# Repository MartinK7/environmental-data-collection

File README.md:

# Environmental-data-collection

##  TASK
Cílem projektu je sestavit systém, který bude schopen monitorovat vybrané meteorologická, případně hydropedologická data a odesílat je na servery pro IoT jako např. Thing Network, ThingSpeak, ubidots, aj. Snahou bude získaná data nejen archivovat, ale poskytnout je některé z předpovědních sítí jako OpenWeather, Weather Underground apod. MP(K)C-M2E: Prostudujte dostupné koncepce pro měření vybraných meteorologických veličin. Prostudujte možnosti řídícího prvku měřícího systému např. AVR, Raspberry Pi, STM32, ESP, aj. a zvolte ideální variantu. Prostudujte vhodné komunikační rozhraní pro přenos dat. Vyberte veškeré komponenty, navrhněte blokové schéma zařízení, sestavte obvodové zapojení, DPS a realizujte je. Při návrhu dbejte na nízkou spotřebu finálního zařízení a odolnost ve venkovním prostředí. MP(K)C-MSE: Zařízení zkompletujte, oživte, naprogramujte obslužné firmwary a zprovozněte sběr dat. Proveďte detailní testování celého systému a porovnejte jej s jinými řešeními. Měřená data poskytněte některé ze sítě pro sběr a předpověď počasí. Pozn.: Systém bude v budoucnu nasazen pro měřící stanici na střeše URELu. Výhodou je zkušenost s vývojem elektroniky a s programováním v jazyce C/C++ nebo Python.

## Basic literary sources
[1] KOUSAL, Martin. IoT monitoring ovzduší. Brno: Vysoké učení technické v Brně, Fakulta elektrotechniky a komunikačních technologií, Ústav radioelektroniky, 2022, 68 s. Bakalářská práce. Vedoucí práce: doc. Ing. Tomáš Frýza, Ph.D.

[2] Weather stations. OpenWeather [online]. 2022 [cit. 2022-05-24]. Dostupné z: https://openweathermap.org/stations

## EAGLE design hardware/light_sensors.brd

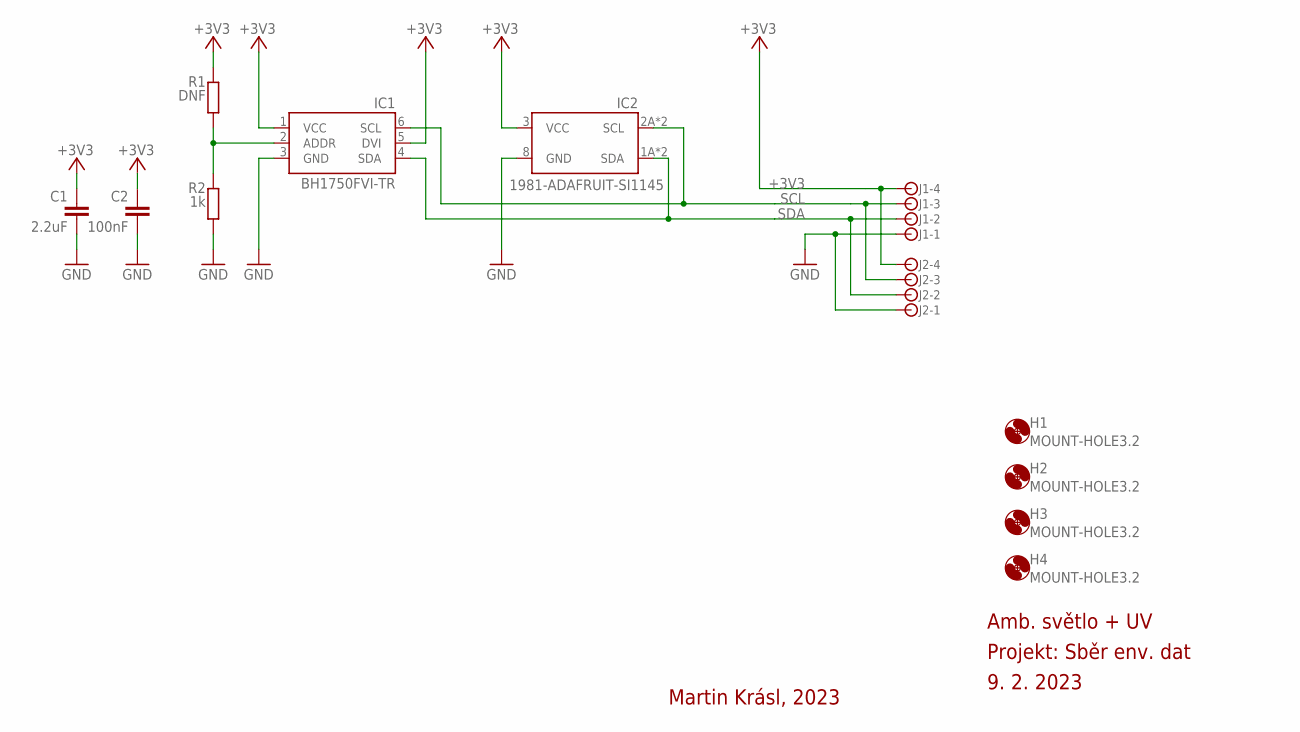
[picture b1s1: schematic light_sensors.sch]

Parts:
C1: 2.2uF; C0805
C2: 100nF; C0402
H1, H2, H3, H4: MOUNT-HOLE3.2; 3,2
IC1: BH1750FVI-TR; WSOF6
IC2: 1981-ADAFRUIT-SI1145
J1, J2: JST-XH-4; B4B-XH-A
R1: DNF; R0402
R2: 1k; R0402

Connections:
+3V3: C1.1, C2.1, IC1.1 (VCC), IC1.5 (DVI), IC2.3 (VCC), J1.4, J2.4, R1.2
GND: C1.2, C2.2, IC1.3 (GND), IC2.8 (GND), J1.1, J2.1, R2.1
unnamed: IC1.2 (ADDR), R1.1, R2.2
SCL: IC1.6 (SCL), IC2.2A (SCL), IC2.2B (SCL), J1.3, J2.3
SDA: IC1.4 (SDA), IC2.1A (SDA), IC2.1B (SDA), J1.2, J2.2

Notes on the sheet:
Amb. světlo + UV
Projekt: Sběr env. dat
9. 2. 2023
Martin Krásl, 2023

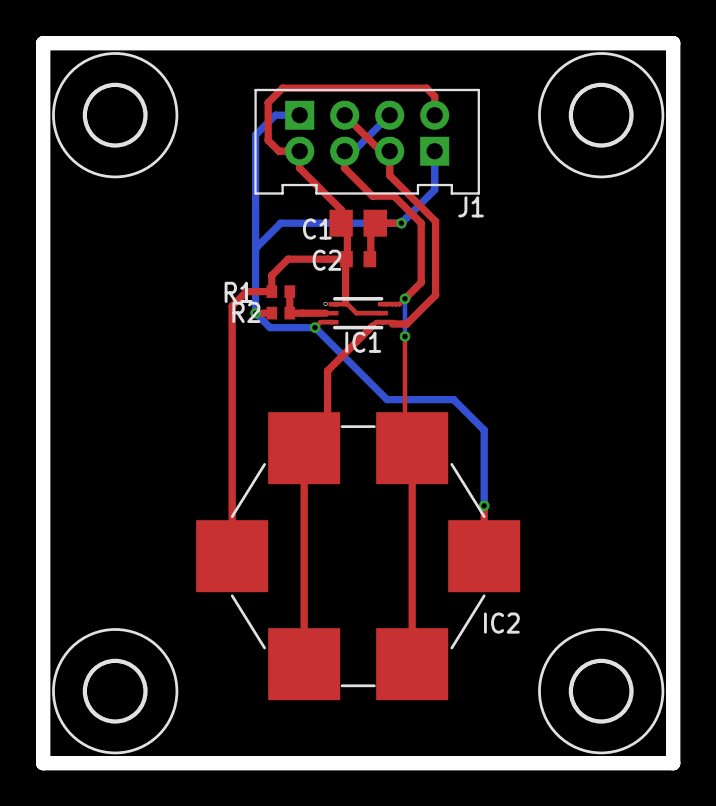
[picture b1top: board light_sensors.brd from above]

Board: 2 copper layers, 35.0 x 40.0 mm, 12 parts (1 on the bottom side), 5 nets.

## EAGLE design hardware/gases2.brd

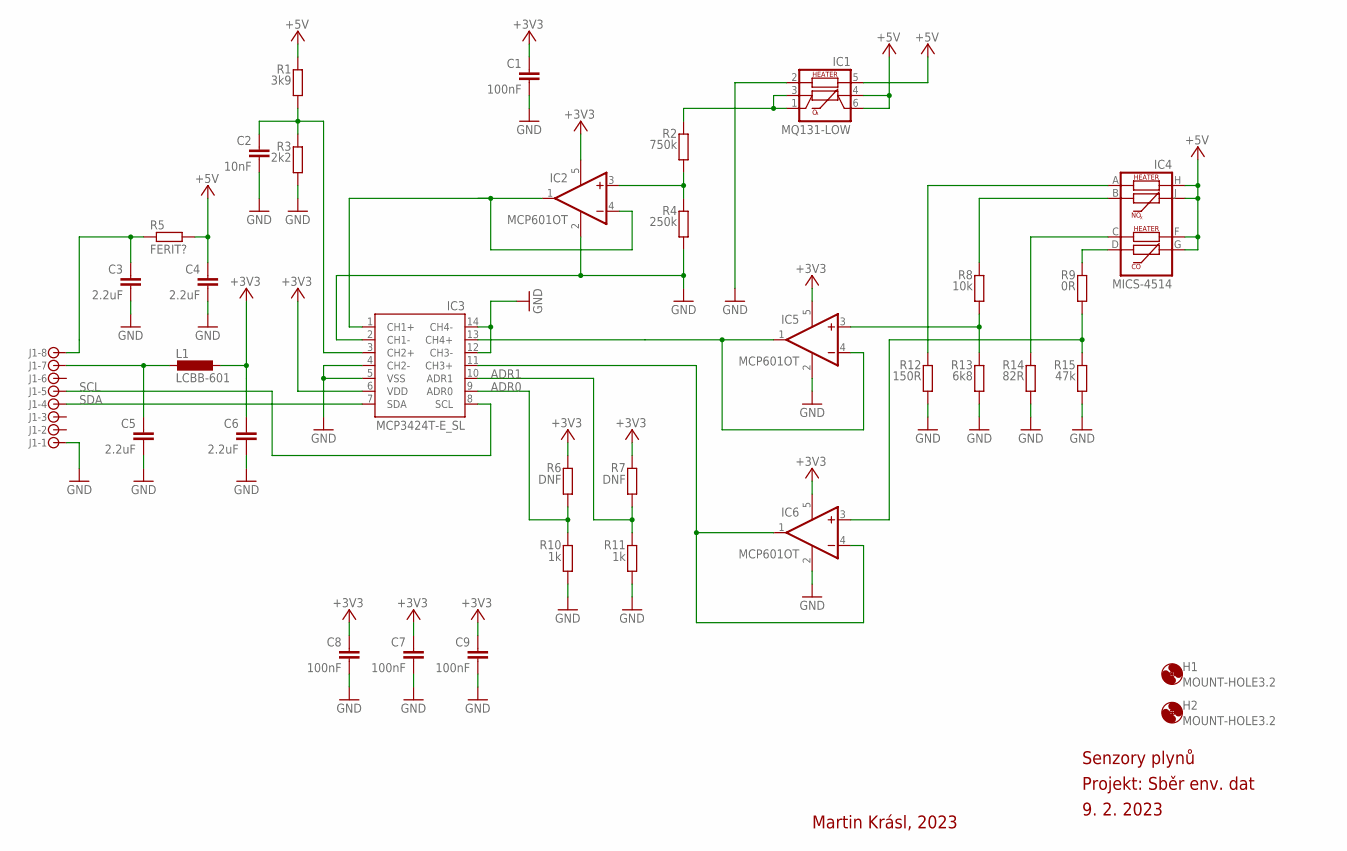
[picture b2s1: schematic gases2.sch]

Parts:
C1, C7, C8, C9: 100nF; C0402
C2: 10nF; C0402
C3, C4, C5, C6: 2.2uF; C0402
H1, H2: MOUNT-HOLE3.2; 3,2
IC1: MQ131-LOW
IC2, IC5, IC6: MCP601OT; SOT23-5
IC3: MCP3424T-E_SL; SOIC127P600X175-14N
IC4: MICS-4514
J1: JST-XH-8; B8B-XH-A
L1: LCBB-601; L2012C
R1: 3k9; R0402
R2: 750k; R0402
R3: 2k2; R0402
R4: 250k; R0402
R5: FERIT?; R0805
R6, R7: DNF; R0402
R8: 10k; R0402
R9: 0R; R0402
R10, R11: 1k; R0402
R12: 150R; R1206
R13: 6k8; R0402
R14: 82R; R1206
R15: 47k; R0402

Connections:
+3V3: C1.1, C6.1, C7.1, C8.1, C9.1, IC2.5 (V+), IC3.6 (VDD), IC5.5 (V+), IC6.5 (V+), L1.1, R6.2, R7.2
+5V: C4.1, IC1.4, IC1.5, IC1.6, IC4.F, IC4.G, IC4.H, IC4.J, R1.2, R5.2
ADR0: IC3.9 (ADR0), R6.1, R10.2
ADR1: IC3.10 (ADR1), R7.1, R11.2
GND: C1.2, C2.2, C3.2, C4.2, C5.2, C6.2, C7.2, C8.2, C9.2, IC1.2, IC2.2 (V-), IC3.2 (CH1-), IC3.4 (CH2-), IC3.5 (VSS), IC3.12 (CH3-), IC3.14 (CH4-), IC5.2 (V-), IC6.2 (V-), J1.1, R3.1, R4.1, R10.1, R11.1, R12.1, R13.1, R14.1, R15.1
unnamed: IC2.1 (OUT), IC2.4 (-IN), IC3.1 (CH1+)
unnamed: C2.1, IC3.3 (CH2+), R1.1, R3.2
unnamed: C3.1, J1.8, R5.1
unnamed: IC2.3 (+IN), R2.1, R4.2
unnamed: IC1.1, IC1.3, R2.2
unnamed: IC4.B, R8.2
unnamed: IC4.D, R9.2
unnamed: IC5.3 (+IN), R8.1, R13.2
unnamed: IC4.A, R12.2
unnamed: IC4.C, R14.2
unnamed: C5.1, J1.7, L1.2
unnamed: IC6.3 (+IN), R9.1, R15.2
unnamed: IC3.13 (CH4+), IC5.1 (OUT), IC5.4 (-IN)
unnamed: IC3.11 (CH3+), IC6.1 (OUT), IC6.4 (-IN)
SCL: IC3.8 (SCL), J1.5
SDA: IC3.7 (SDA), J1.4

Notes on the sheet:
Senzory plynů
Projekt: Sběr env. dat
9. 2. 2023
Martin Krásl, 2023

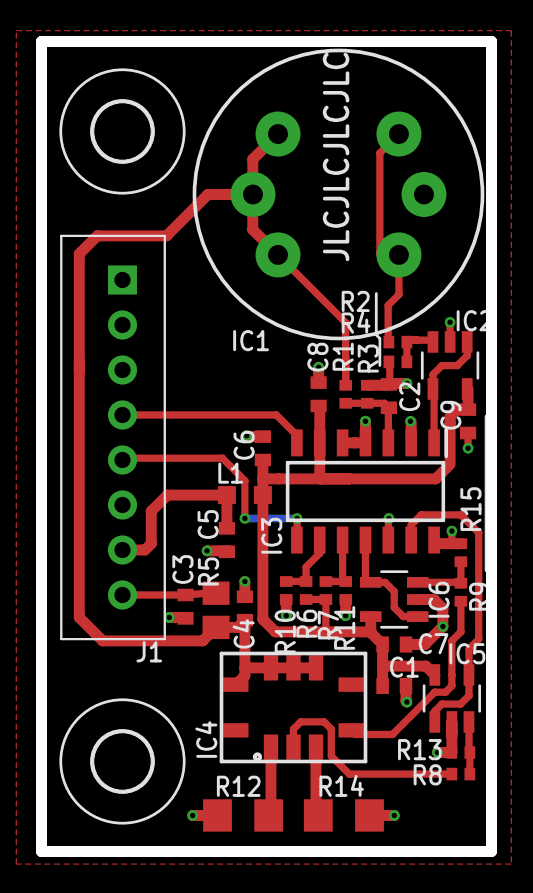
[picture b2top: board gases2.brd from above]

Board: 2 copper layers, 25.0 x 45.0 mm, 34 parts (0 on the bottom side), 21 nets.

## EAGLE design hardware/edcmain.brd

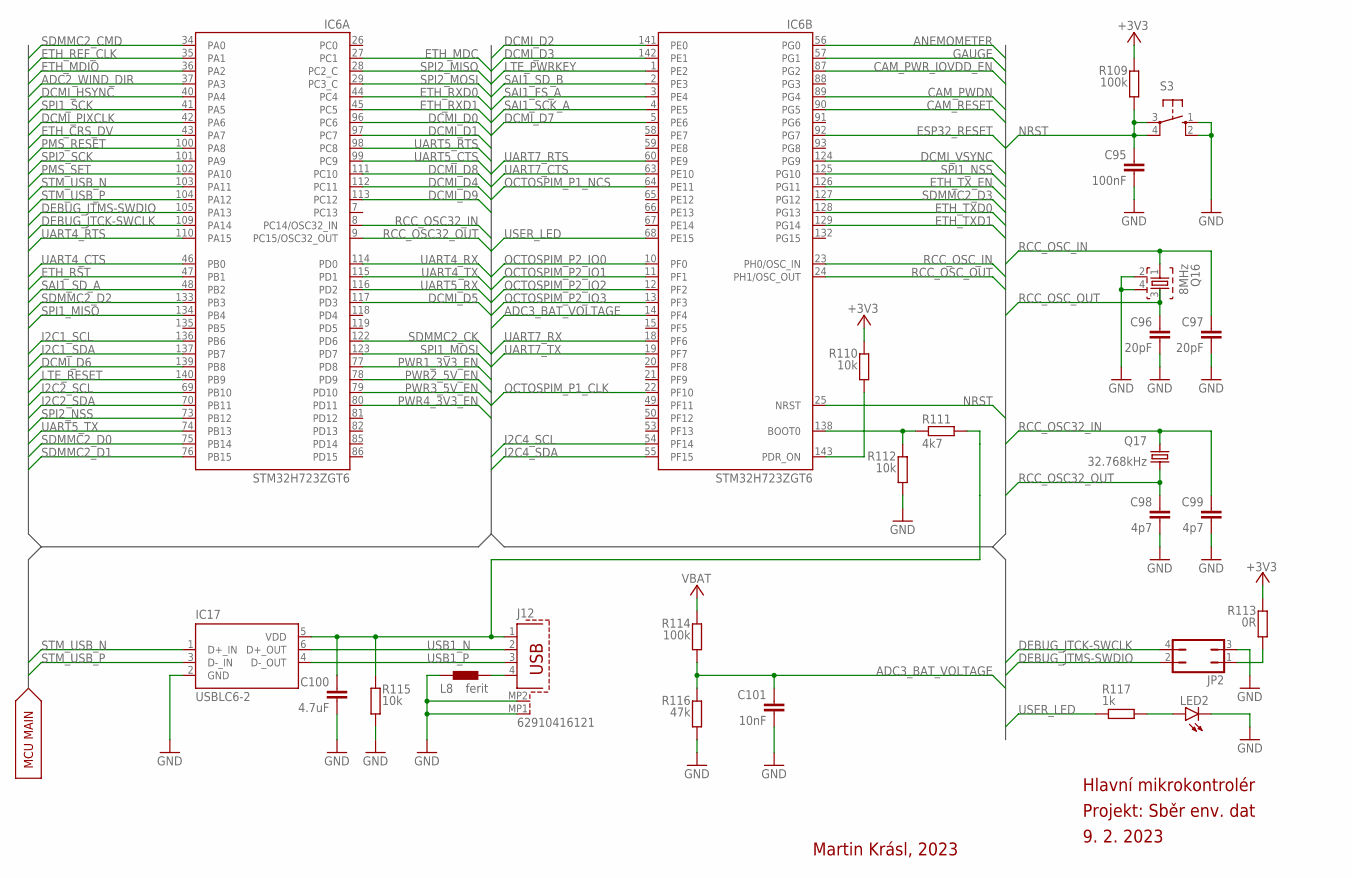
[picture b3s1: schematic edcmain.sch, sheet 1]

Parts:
C95: 100nF; C0402
C96, C97: 20pF; C0402
C98, C99: 4p7; C0402
C100: 4.7uF; C0402
C101: 10nF; C0402
IC6: STM32H723ZGT6; QFP50P2200X2200X160-144N
IC17: USBLC6-2; SOT23-6
J12: 62910416121
JP2: JP2Q
L8: ferit; 0402
LED2: LEDCHIP-LED0805; CHIP-LED0805
Q16: 8MHz; CRYSTAL3.2X2.5
Q17: 32.768kHz; NX3215SA32768KEXS00AMU00003
R109, R114: 100k; R0402
R110, R112, R115: 10k; R0402
R111: 4k7; R0402
R113: 0R; R0402
R116: 47k; R0402
R117: 1k; R0402
S3: 10-XX; B3F-10XX

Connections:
+3V3: R109.2, R110.2, R113.2; also elsewhere on the board
ADC2_WIND_DIR: IC6.37 (PA3); also elsewhere on the board
ADC3_BAT_VOLTAGE: C101.1, IC6.14 (PF4), R114.1, R116.2
ANEMOMETER: IC6.56 (PG0); also elsewhere on the board
CAM_PWDN: IC6.89 (PG4); also elsewhere on the board
CAM_PWR_IOVDD_EN: IC6.87 (PG2); also elsewhere on the board
CAM_RESET: IC6.90 (PG5); also elsewhere on the board
DCMI_D0: IC6.96 (PC6); also elsewhere on the board
DCMI_D1: IC6.97 (PC7); also elsewhere on the board
DCMI_D2: IC6.141 (PE0); also elsewhere on the board
DCMI_D3: IC6.142 (PE1); also elsewhere on the board
DCMI_D4: IC6.112 (PC11); also elsewhere on the board
DCMI_D5: IC6.117 (PD3); also elsewhere on the board
DCMI_D6: IC6.139 (PB8); also elsewhere on the board
DCMI_D7: IC6.5 (PE6); also elsewhere on the board
DCMI_D8: IC6.111 (PC10); also elsewhere on the board
DCMI_D9: IC6.113 (PC12); also elsewhere on the board
DCMI_HSYNC: IC6.40 (PA4); also elsewhere on the board
DCMI_PIXCLK: IC6.42 (PA6); also elsewhere on the board
DCMI_VSYNC: IC6.124 (PG9); also elsewhere on the board
DEBUG_JTCK-SWCLK: IC6.109 (PA14), JP2.4
DEBUG_JTMS-SWDIO: IC6.105 (PA13), JP2.2
ESP32_RESET: IC6.92 (PG7); also elsewhere on the board
ETH_CRS_DV: IC6.43 (PA7); also elsewhere on the board
ETH_MDC: IC6.27 (PC1); also elsewhere on the board
ETH_MDIO: IC6.36 (PA2); also elsewhere on the board
ETH_REF_CLK: IC6.35 (PA1); also elsewhere on the board
ETH_RST: IC6.47 (PB1); also elsewhere on the board
ETH_RXD0: IC6.44 (PC4); also elsewhere on the board
ETH_RXD1: IC6.45 (PC5); also elsewhere on the board
ETH_TXD0: IC6.128 (PG13); also elsewhere on the board
ETH_TXD1: IC6.129 (PG14); also elsewhere on the board
ETH_TX_EN: IC6.126 (PG11); also elsewhere on the board
GAUGE: IC6.57 (PG1); also elsewhere on the board
GND: C95.2, C96.2, C97.2, C98.2, C99.2, C100.2, C101.2, IC17.2 (GND), J12.MP1, J12.MP2, JP2.3, L8.1, LED2.C, Q16.2, Q16.4, R112.1, R115.1, R116.1, S3.1 (S), S3.2 (S1); also elsewhere on the board
I2C1_SCL: IC6.136 (PB6); also elsewhere on the board
I2C1_SDA: IC6.137 (PB7); also elsewhere on the board
I2C2_SCL: IC6.69 (PB10); also elsewhere on the board
I2C2_SDA: IC6.70 (PB11); also elsewhere on the board
I2C4_SCL: IC6.54 (PF14); also elsewhere on the board
I2C4_SDA: IC6.55 (PF15); also elsewhere on the board
LTE_PWRKEY: IC6.1 (PE2); also elsewhere on the board
LTE_RESET: IC6.140 (PB9); also elsewhere on the board
unnamed: C100.1, IC17.5 (VDD), J12.1, R111.2, R115.2
unnamed: LED2.A, R117.2
unnamed: IC6.143 (PDR_ON), R110.1
unnamed: IC6.138 (BOOT0), R111.1, R112.2
unnamed: J12.4, L8.2
unnamed: JP2.1, R113.1
NRST: C95.1, IC6.25 (NRST), R109.1, S3.3, S3.4 (P1)
OCTOSPIM_P1_CLK: IC6.22 (PF10); also elsewhere on the board
OCTOSPIM_P1_NCS: IC6.64 (PE11); also elsewhere on the board
OCTOSPIM_P2_IO0: IC6.10 (PF0); also elsewhere on the board
OCTOSPIM_P2_IO1: IC6.11 (PF1); also elsewhere on the board
OCTOSPIM_P2_IO2: IC6.12 (PF2); also elsewhere on the board
OCTOSPIM_P2_IO3: IC6.13 (PF3); also elsewhere on the board
PMS_RESET: IC6.100 (PA8); also elsewhere on the board
PMS_SET: IC6.102 (PA10); also elsewhere on the board
PWR1_3V3_EN: IC6.77 (PD8); also elsewhere on the board
PWR2_5V_EN: IC6.78 (PD9); also elsewhere on the board
PWR3_5V_EN: IC6.79 (PD10); also elsewhere on the board
PWR4_3V3_EN: IC6.80 (PD11); also elsewhere on the board
RCC_OSC32_IN: C99.1, IC6.8 (PC14/OSC32_IN), Q17.2
RCC_OSC32_OUT: C98.1, IC6.9 (PC15/OSC32_OUT), Q17.1
RCC_OSC_IN: C97.1, IC6.23 (PH0/OSC_IN), Q16.1
RCC_OSC_OUT: C96.1, IC6.24 (PH1/OSC_OUT), Q16.3
SAI1_FS_A: IC6.3 (PE4); also elsewhere on the board
SAI1_SCK_A: IC6.4 (PE5); also elsewhere on the board
SAI1_SD_A: IC6.48 (PB2); also elsewhere on the board
SAI1_SD_B: IC6.2 (PE3); also elsewhere on the board
SDMMC2_CK: IC6.122 (PD6); also elsewhere on the board
SDMMC2_CMD: IC6.34 (PA0); also elsewhere on the board
SDMMC2_D0: IC6.75 (PB14); also elsewhere on the board
SDMMC2_D1: IC6.76 (PB15); also elsewhere on the board
SDMMC2_D2: IC6.133 (PB3); also elsewhere on the board
SDMMC2_D3: IC6.127 (PG12); also elsewhere on the board
SPI1_MISO: IC6.134 (PB4); also elsewhere on the board
SPI1_MOSI: IC6.123 (PD7); also elsewhere on the board
SPI1_NSS: IC6.125 (PG10); also elsewhere on the board
SPI1_SCK: IC6.41 (PA5); also elsewhere on the board
SPI2_MISO: IC6.28 (PC2_C); also elsewhere on the board
SPI2_MOSI: IC6.29 (PC3_C); also elsewhere on the board
SPI2_NSS: IC6.73 (PB12); also elsewhere on the board
SPI2_SCK: IC6.101 (PA9); also elsewhere on the board
STM_USB_N: IC6.103 (PA11), IC17.1 (D+_IN)
STM_USB_P: IC6.104 (PA12), IC17.3 (D-_IN)
UART4_CTS: IC6.46 (PB0); also elsewhere on the board
UART4_RTS: IC6.110 (PA15); also elsewhere on the board
UART4_RX: IC6.114 (PD0); also elsewhere on the board
UART4_TX: IC6.115 (PD1); also elsewhere on the board
UART5_CTS: IC6.99 (PC9); also elsewhere on the board
UART5_RTS: IC6.98 (PC8); also elsewhere on the board
UART5_RX: IC6.116 (PD2); also elsewhere on the board
UART5_TX: IC6.74 (PB13); also elsewhere on the board
UART7_CTS: IC6.63 (PE10); also elsewhere on the board
UART7_RTS: IC6.60 (PE9); also elsewhere on the board
UART7_RX: IC6.18 (PF6); also elsewhere on the board
UART7_TX: IC6.19 (PF7); also elsewhere on the board
USB1_N: IC17.6 (D+_OUT), J12.2
USB1_P: IC17.4 (D-_OUT), J12.3
USER_LED: IC6.68 (PE15), R117.1
VBAT: R114.2; also elsewhere on the board

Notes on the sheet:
MCU MAIN
Hlavní mikrokontrolér
Projekt: Sběr env. dat
9. 2. 2023
Martin Krásl, 2023

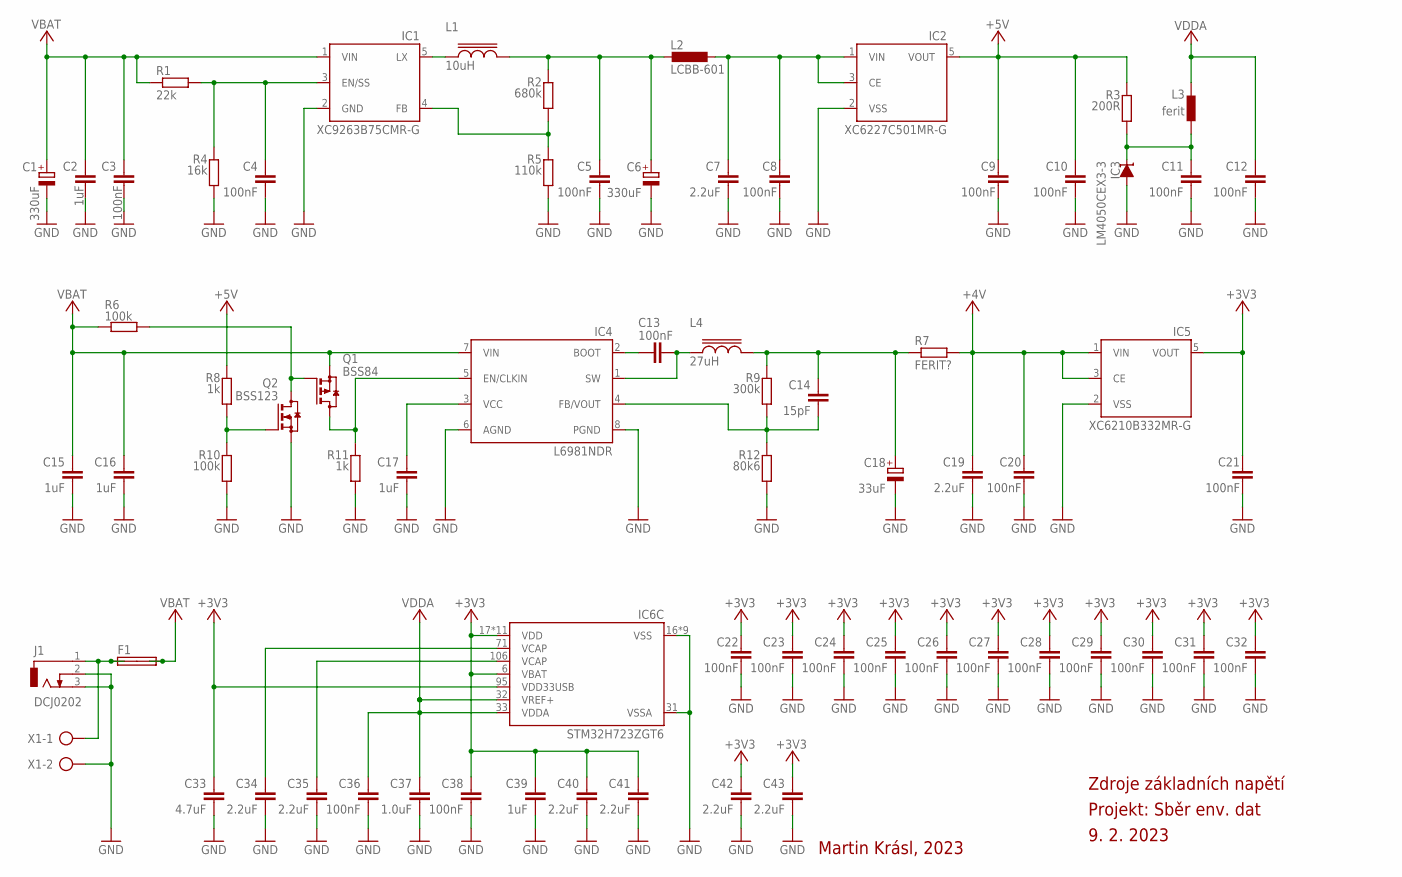
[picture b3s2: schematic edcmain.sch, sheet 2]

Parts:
C1, C6: 330uF; PANASONIC_G
C2, C15, C16: 1uF; C0805
C3, C4, C5, C8, C9, C10, C11, C12, C13, C20, C21, C22, C23, C24, C25, C26, C27, C28, C29, C30, C31, C32, C36, C38: 100nF; C0402
C7, C34, C35, C43: 2.2uF; C0805
C14: 15pF; C0402
C17, C39: 1uF; C0402
C18: 33uF; PANASONIC_G
C19, C40, C41, C42: 2.2uF; C0402
C33: 4.7uF; C0402
C37: 1.0uF; C0402
F1: SHK20L
IC1: XC9263B75CMR-G; SOT95P280X130-5N
IC2: XC6227C501MR-G; SOT95P280X130-5N
IC3: LM4050CEX3-3; SC70-3
IC4: L6981NDR; SOIC127P600X175-8N
IC5: XC6210B332MR-G; SOT95P280X130-5N
IC6: STM32H723ZGT6; QFP50P2200X2200X160-144N
IMG1: IMAGEPRINT; RD_14_24_PRINT
J1: DCJ0202
L1: 10uH; L6
L2: LCBB-601; L2012C
L3: ferit; 0402
L4: 27uH; L6
Q1: BSS84; SOT23
Q2: BSS123; SOT23
R1: 22k; R0402
R2: 680k; R0402
R3: 200R; R0402
R4: 16k; R0402
R5: 110k; R0402
R6, R10: 100k; R0402
R7: FERIT?; R2010
R8, R11: 1k; R0402
R9: 300k; R0402
R12: 80k6; R0402
X1: AK500/2

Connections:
+3V3: C21.1, C22.1, C23.1, C24.1, C25.1, C26.1, C27.1, C28.1, C29.1, C30.1, C31.1, C32.1, C33.1, C38.1, C39.1, C40.1, C41.1, C42.1, C43.1, IC5.5 (VOUT), IC6.6 (VBAT), IC6.17 (VDD), IC6.30 (VDD), IC6.39 (VDD), IC6.52 (VDD), IC6.62 (VDD), IC6.72 (VDD), IC6.84 (VDD), IC6.95 (VDD33USB), IC6.108 (VDD), IC6.121 (VDD), IC6.131 (VDD), IC6.144 (VDD); also elsewhere on the board
+4V: C19.1, C20.1, IC5.1 (VIN), IC5.3 (CE), R7.2; also elsewhere on the board
+5V: C9.1, C10.1, IC2.5 (VOUT), R3.2, R8.2; also elsewhere on the board
GND: C1.-, C2.2, C3.2, C4.2, C5.2, C6.-, C7.2, C8.2, C9.2, C10.2, C11.2, C12.2, C15.2, C16.2, C17.2, C18.-, C19.2, C20.2, C21.2, C22.2, C23.2, C24.2, C25.2, C26.2, C27.2, C28.2, C29.2, C30.2, C31.2, C32.2, C33.2, C34.2, C35.2, C36.2, C37.2, C38.2, C39.2, C40.2, C41.2, C42.2, C43.2, IC1.2 (GND), IC2.2 (VSS), IC3.1 (A), IC4.6 (AGND), IC4.8 (PGND), IC5.2 (VSS), IC6.16 (VSS), IC6.31 (VSSA), IC6.38 (VSS), IC6.51 (VSS), IC6.61 (VSS), IC6.83 (VSS), IC6.94 (VSS), IC6.107 (VSS), IC6.120 (VSS), IC6.130 (VSS), J1.2, J1.3, Q2.2 (S), R4.1, R5.1, R10.1, R11.1, R12.1, X1.2; also elsewhere on the board
unnamed: F1.1A, F1.1B, J1.1, X1.1
unnamed: C34.1, IC6.71 (VCAP)
unnamed: C35.1, IC6.106 (VCAP)
unnamed: C11.1, IC3.2 (C), L3.1, R3.1
unnamed: C17.1, IC4.3 (VCC)
unnamed: C7.1, C8.1, IC2.1 (VIN), IC2.3 (CE), L2.1
unnamed: C5.1, C6.+, L1.P$2, L2.2, R2.2
unnamed: IC1.5 (LX), L1.P$1
unnamed: IC1.4 (FB), R2.1, R5.2
unnamed: C4.1, IC1.3 (EN/SS), R1.2, R4.2
unnamed: C14.2, IC4.4 (FB/VOUT), R9.1, R12.2
unnamed: C13.1, IC4.2 (BOOT)
unnamed: C13.2, IC4.1 (SW), L4.P$1
unnamed: C14.1, C18.+, L4.P$2, R7.1, R9.2
unnamed: Q1.1 (G), Q2.3 (D), R6.2
unnamed: IC4.5 (EN/CLKIN), Q1.3 (D), R11.2
unnamed: Q2.1 (G), R8.1, R10.2
VBAT: C1.+, C2.1, C3.1, C15.1, C16.1, F1.2A, F1.2B, IC1.1 (VIN), IC4.7 (VIN), Q1.2 (S), R1.1, R6.1; also elsewhere on the board
VDDA: C12.1, C36.1, C37.1, IC6.32 (VREF+), IC6.33 (VDDA), L3.2

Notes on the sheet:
Zdroje základních napětí
Projekt: Sběr env. dat
9. 2. 2023
Martin Krásl, 2023

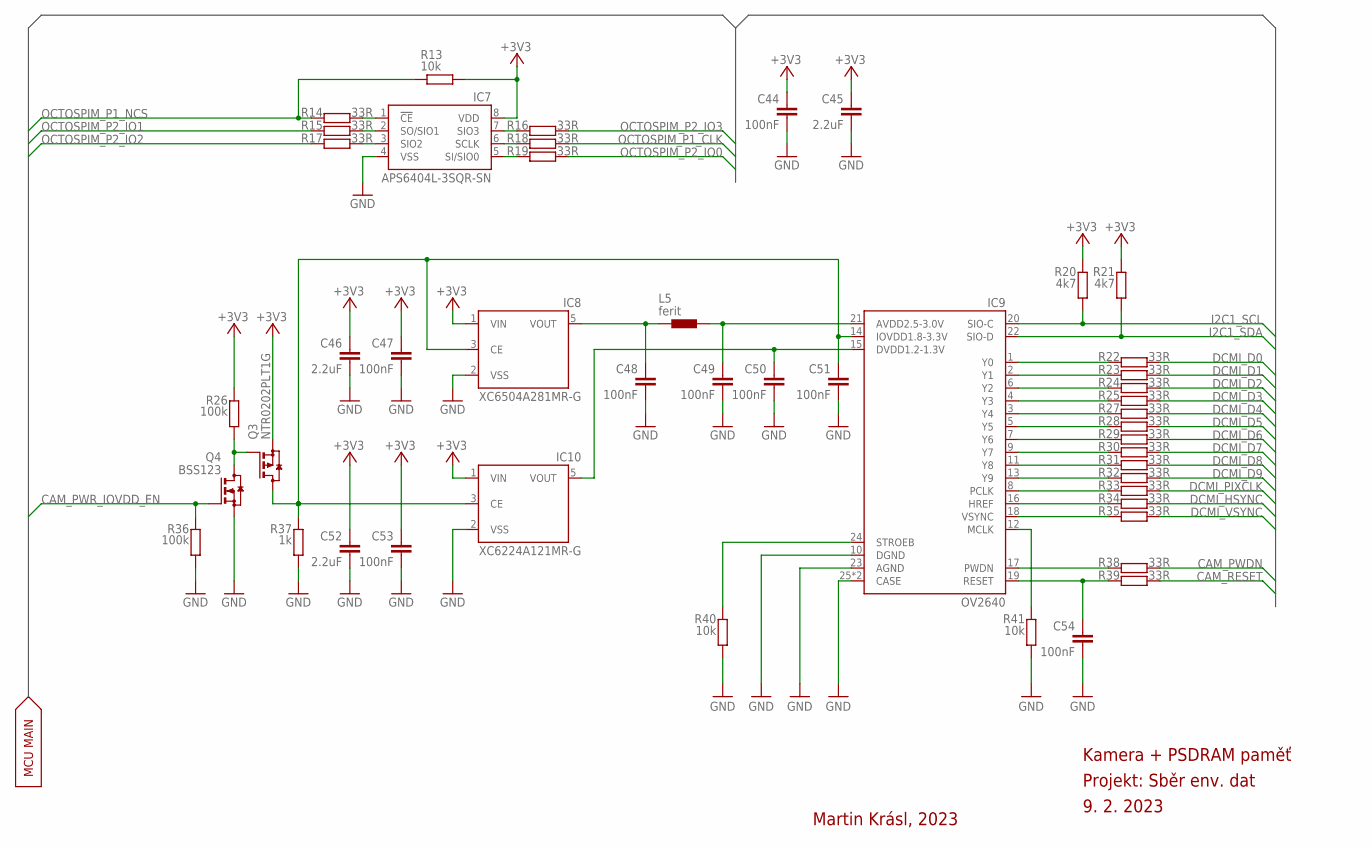
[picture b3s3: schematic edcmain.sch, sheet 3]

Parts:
C44, C47, C48, C49, C50, C51, C53, C54: 100nF; C0402
C45, C46: 2.2uF; C0402
C52: 2.2uF; C0805
IC7: APS6404L-3SQR-SN; SOP08
IC8: XC6504A281MR-G; SOT95P280X130-5N
IC9: OV2640; XF2M-2415-1A-SWAP
IC10: XC6224A121MR-G; SOT95P280X130-5N
L5: ferit; 0402
Q3: NTR0202PLT1G; SOT23
Q4: BSS123; SOT23
R13, R40, R41: 10k; R0402
R14, R15, R16, R17, R18, R19, R22, R23, R24, R25, R27, R28, R29, R30, R31, R32, R33, R34, R35, R38, R39: 33R; R0402
R20, R21: 4k7; R0402
R26, R36: 100k; R0402
R37: 1k; R0402

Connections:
+3V3: C44.1, C45.1, C46.1, C47.1, C52.1, C53.1, IC7.8 (VDD), IC8.1 (VIN), IC10.1 (VIN), Q3.2 (S), R13.2, R20.2, R21.2, R26.2; also elsewhere on the board
CAM_PWDN: R38.2; also elsewhere on the board
CAM_PWR_IOVDD_EN: Q4.1 (G), R36.2; also elsewhere on the board
CAM_RESET: R39.2; also elsewhere on the board
DCMI_D0: R22.2; also elsewhere on the board
DCMI_D1: R23.2; also elsewhere on the board
DCMI_D2: R24.2; also elsewhere on the board
DCMI_D3: R25.2; also elsewhere on the board
DCMI_D4: R27.2; also elsewhere on the board
DCMI_D5: R28.2; also elsewhere on the board
DCMI_D6: R29.2; also elsewhere on the board
DCMI_D7: R30.2; also elsewhere on the board
DCMI_D8: R31.2; also elsewhere on the board
DCMI_D9: R32.2; also elsewhere on the board
DCMI_HSYNC: R34.2; also elsewhere on the board
DCMI_PIXCLK: R33.2; also elsewhere on the board
DCMI_VSYNC: R35.2; also elsewhere on the board
GND: C44.2, C45.2, C46.2, C47.2, C48.2, C49.2, C50.2, C51.2, C52.2, C53.2, C54.2, IC7.4 (VSS), IC8.2 (VSS), IC9.10 (DGND), IC9.23 (AGND), IC9.25 (CASE), IC9.26 (CASE), IC10.2 (VSS), Q4.2 (S), R36.1, R37.1, R40.1, R41.1; also elsewhere on the board
I2C1_SCL: IC9.20 (SIO-C), R20.1; also elsewhere on the board
I2C1_SDA: IC9.22 (SIO-D), R21.1; also elsewhere on the board
unnamed: IC9.1 (Y0), R22.1
unnamed: IC9.2 (Y1), R23.1
unnamed: IC9.6 (Y2), R24.1
unnamed: IC9.4 (Y3), R25.1
unnamed: IC9.3 (Y4), R27.1
unnamed: IC9.5 (Y5), R28.1
unnamed: IC9.7 (Y6), R29.1
unnamed: IC9.9 (Y7), R30.1
unnamed: IC9.11 (Y8), R31.1
unnamed: IC9.13 (Y9), R32.1
unnamed: IC7.1 (!CE!), R14.2
unnamed: IC7.2 (SO/SIO1), R15.2
unnamed: IC7.3 (SIO2), R17.2
unnamed: IC7.7 (SIO3), R16.1
unnamed: IC7.6 (SCLK), R18.1
unnamed: IC7.5 (SI/SIO0), R19.1
unnamed: IC9.18 (VSYNC), R35.1
unnamed: IC9.16 (HREF), R34.1
unnamed: IC9.8 (PCLK), R33.1
unnamed: C48.1, IC8.5 (VOUT), L5.1
unnamed: C49.1, IC9.21 (AVDD2.5-3.0V), L5.2
unnamed: C50.1, IC9.15 (DVDD1.2-1.3V), IC10.5 (VOUT)
unnamed: IC9.24 (STROEB), R40.2
unnamed: IC9.17 (PWDN), R38.1
unnamed: IC9.12 (MCLK), R41.2
unnamed: C54.1, IC9.19 (RESET), R39.1
unnamed: Q3.1 (G), Q4.3 (D), R26.1
unnamed: C51.1, IC8.3 (CE), IC9.14 (IOVDD1.8-3.3V), IC10.3 (CE), Q3.3 (D), R37.2
OCTOSPIM_P1_CLK: R18.2; also elsewhere on the board
OCTOSPIM_P1_NCS: R13.1, R14.1; also elsewhere on the board
OCTOSPIM_P2_IO0: R19.2; also elsewhere on the board
OCTOSPIM_P2_IO1: R15.1; also elsewhere on the board
OCTOSPIM_P2_IO2: R17.1; also elsewhere on the board
OCTOSPIM_P2_IO3: R16.2; also elsewhere on the board

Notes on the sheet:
MCU MAIN
Kamera + PSDRAM paměť
Projekt: Sběr env. dat
9. 2. 2023
Martin Krásl, 2023

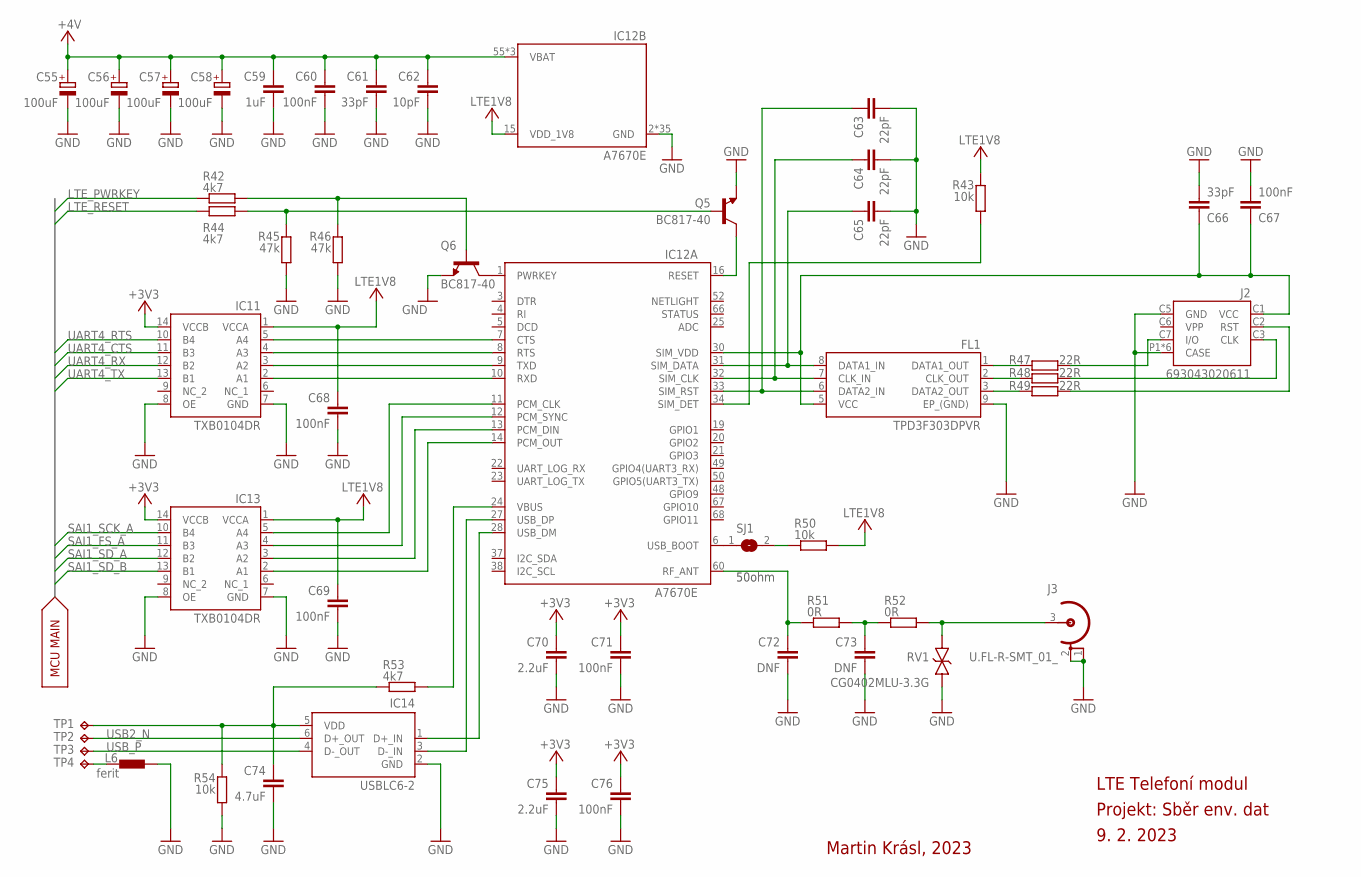
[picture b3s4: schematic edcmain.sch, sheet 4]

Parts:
C55, C56, C57, C58: 100uF; B/3528-21R
C59: 1uF; C0805
C60, C67, C68, C69, C71, C76: 100nF; C0402
C61, C66: 33pF; C0402
C62: 10pF; C0402
C63, C64, C65: 22pF; C0402
C70, C75: 2.2uF; C0402
C72, C73: DNF; C0402
C74: 4.7uF; C0402
FL1: TPD3F303DPVR; SON50P160X210X65-9N
IC11, IC13: TXB0104DR; SOIC127P600X175-14N
IC12: A7670E; A7670CLNSC
IC14: USBLC6-2; SOT23-6
J2: 693043020611
J3: U.FL-R-SMT_01_; UFLRSMT01
L6: ferit; 0402
Q5, Q6: BC817-40; SOT23-BEC
R42, R44, R53: 4k7; R0402
R43, R50, R54: 10k; R0402
R45, R46: 47k; R0402
R47, R48, R49: 22R; R0402
R51, R52: 0R; R0402
RV1: CG0402MLU-3.3G; VARC1005X41N
SJ1: SJ
TP1, TP2, TP3, TP4: TPB1,27; B1,27

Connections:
50OHM_1: C72.1, IC12.60 (RF_ANT), R51.1
50OHM_2: C73.1, R51.2, R52.1
50OHM_3: J3.3 (SIG), R52.2, RV1.1
+3V3: C70.1, C71.1, C75.1, C76.1, IC11.14 (VCCB), IC13.14 (VCCB); also elsewhere on the board
+4V: C55.+, C56.+, C57.+, C58.+, C59.1, C60.1, C61.1, C62.1, IC12.55 (VBAT), IC12.56 (VBAT), IC12.57 (VBAT); also elsewhere on the board
GND: C55.-, C56.-, C57.-, C58.-, C59.2, C60.2, C61.2, C62.2, C63.2, C64.2, C65.2, C66.2, C67.2, C68.2, C69.2, C70.2, C71.2, C72.2, C73.2, C74.2, C75.2, C76.2, FL1.9 (EP_(GND)), IC11.7 (GND), IC11.8 (OE), IC12.2 (GND), IC12.17 (GND), IC12.18 (GND), IC12.29 (GND), IC12.39 (GND), IC12.45 (GND), IC12.46 (GND), IC12.54 (GND), IC12.58 (GND), IC12.59 (GND), IC12.61 (GND), IC12.62 (GND), IC12.63 (GND), IC12.64 (GND), IC12.65 (GND), IC12.69 (GND), IC12.70 (GND), IC12.71 (GND), IC12.72 (GND), IC12.73 (GND), IC12.74 (GND), IC12.75 (GND), IC12.76 (GND), IC12.77 (GND), IC12.78 (GND), IC12.79 (GND), IC12.80 (GND), IC12.81 (GND), IC12.82 (GND), IC12.83 (GND), IC12.84 (GND), IC12.85 (GND), IC12.86 (GND), IC12.87 (GND), IC12.88 (GND), IC13.7 (GND), IC13.8 (OE), IC14.2 (GND), J2.C5 (GND), J2.P1 (CASE), J2.P2 (CASE), J2.P3 (CASE), J2.P4 (CASE), J2.P5 (CASE), J2.P6 (CASE), J3.1 (GND), J3.2 (GND), L6.1, Q5.E, Q6.E, R45.1, R46.1, R54.1, RV1.2; also elsewhere on the board
LTE1V8: C68.1, C69.1, IC11.1 (VCCA), IC12.15 (VDD_1V8), IC13.1 (VCCA), R43.2, R50.2
LTE_PWRKEY: R42.1; also elsewhere on the board
LTE_RESET: R44.1; also elsewhere on the board
unnamed: IC11.5 (A4), IC12.7 (CTS)
unnamed: IC11.4 (A3), IC12.8 (RTS)
unnamed: IC11.3 (A2), IC12.9 (TXD)
unnamed: IC11.2 (A1), IC12.10 (RXD)
unnamed: IC12.11 (PCM_CLK), IC13.5 (A4)
unnamed: IC12.12 (PCM_SYNC), IC13.4 (A3)
unnamed: IC12.13 (PCM_DIN), IC13.3 (A2)
unnamed: IC12.14 (PCM_OUT), IC13.2 (A1)
unnamed: C66.1, C67.1, FL1.5 (VCC), IC12.30 (SIM_VDD), J2.C1 (VCC)
unnamed: J2.C2 (RST), R49.2
unnamed: J2.C3 (CLK), R48.2
unnamed: J2.C7 (I/O), R47.2
unnamed: C63.1, FL1.6 (DATA2_IN), IC12.33 (SIM_RST)
unnamed: C64.1, FL1.7 (CLK_IN), IC12.32 (SIM_CLK)
unnamed: C65.1, FL1.8 (DATA1_IN), IC12.31 (SIM_DATA)
unnamed: IC12.34 (SIM_DET), R43.1
unnamed: C74.1, IC14.5 (VDD), R53.1, R54.2, TP1.TP
unnamed: L6.2, TP4.TP
unnamed: IC12.27 (USB_DP), IC14.3 (D-_IN)
unnamed: IC12.28 (USB_DM), IC14.1 (D+_IN)
unnamed: IC12.24 (VBUS), R53.2
unnamed: IC12.1 (PWRKEY), Q6.C
unnamed: IC12.6 (USB_BOOT), SJ1.1
unnamed: Q6.B, R42.2, R46.2
unnamed: IC12.16 (RESET), Q5.C
unnamed: R50.1, SJ1.2
unnamed: Q5.B, R44.2, R45.2
unnamed: FL1.3 (DATA2_OUT), R49.1
unnamed: FL1.2 (CLK_OUT), R48.1
unnamed: FL1.1 (DATA1_OUT), R47.1
SAI1_FS_A: IC13.11 (B3); also elsewhere on the board
SAI1_SCK_A: IC13.10 (B4); also elsewhere on the board
SAI1_SD_A: IC13.12 (B2); also elsewhere on the board
SAI1_SD_B: IC13.13 (B1); also elsewhere on the board
UART4_CTS: IC11.11 (B3); also elsewhere on the board
UART4_RTS: IC11.10 (B4); also elsewhere on the board
UART4_RX: IC11.12 (B2); also elsewhere on the board
UART4_TX: IC11.13 (B1); also elsewhere on the board
USB2_N: IC14.6 (D+_OUT), TP2.TP
USB_P: IC14.4 (D-_OUT), TP3.TP

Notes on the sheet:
MCU MAIN
50ohm
LTE Telefoní modul
Projekt: Sběr env. dat
9. 2. 2023
Martin Krásl, 2023

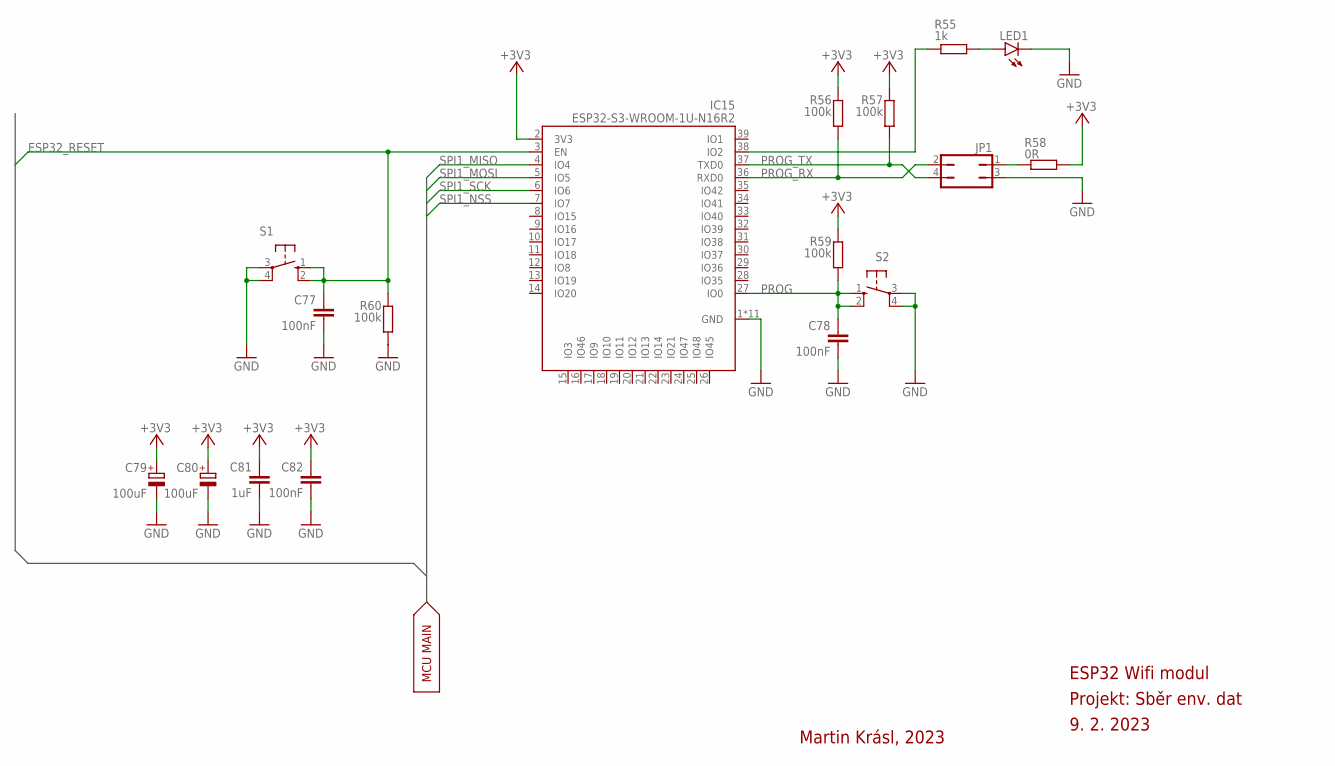
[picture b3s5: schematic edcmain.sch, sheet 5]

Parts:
C77, C78, C82: 100nF; C0402
C79, C80: 100uF; B/3528-21R
C81: 1uF; C0805
IC15: ESP32-S3-WROOM-1U-N16R2; ESP32S3WROOM1UN16R2
JP1: JP2Q
LED1: LEDCHIP-LED0805; CHIP-LED0805
R55: 1k; R0402
R56, R57, R59, R60: 100k; R0402
R58: 0R; R0402
S1, S2: 10-XX; B3F-10XX

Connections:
+3V3: C79.+, C80.+, C81.1, C82.1, IC15.2 (3V3), R56.2, R57.2, R58.2, R59.2; also elsewhere on the board
ESP32_RESET: C77.1, IC15.3 (EN), R60.2, S1.1 (S), S1.2 (S1); also elsewhere on the board
GND: C77.2, C78.2, C79.-, C80.-, C81.2, C82.2, IC15.1 (GND), IC15.40 (GND), IC15.41 (GND), IC15.42 (GND), IC15.43 (GND), IC15.44 (GND), IC15.45 (GND), IC15.46 (GND), IC15.47 (GND), IC15.48 (GND), IC15.49 (GND), JP1.3, LED1.C, R60.1, S1.3, S1.4 (P1), S2.3, S2.4 (P1); also elsewhere on the board
unnamed: JP1.1, R58.1
unnamed: LED1.A, R55.2
unnamed: IC15.38 (IO2), R55.1
PROG: C78.1, IC15.27 (IO0), R59.1, S2.1 (S), S2.2 (S1)
PROG_RX: IC15.36 (RXD0), JP1.2, R56.1
PROG_TX: IC15.37 (TXD0), JP1.4, R57.1
SPI1_MISO: IC15.4 (IO4); also elsewhere on the board
SPI1_MOSI: IC15.5 (IO5); also elsewhere on the board
SPI1_NSS: IC15.7 (IO7); also elsewhere on the board
SPI1_SCK: IC15.6 (IO6); also elsewhere on the board

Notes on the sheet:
MCU MAIN
ESP32 Wifi modul
Projekt: Sběr env. dat
9. 2. 2023
Martin Krásl, 2023
